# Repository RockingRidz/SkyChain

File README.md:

# SkyChain

## Current project files

- [KiCad project](pcb/SkyChain.kicad_pro), [schematic](pcb/SkyChain.kicad_sch), and [PCB](pcb/SkyChain.kicad_pcb)
- [Current Gerbers and drill files](production/gerbers.zip) — the single fabrication ZIP
- [Firmware](firmware/firmware.ino) — buttons on GPIO10 and GPIO3
- [Editable enclosure sources and STL files](cad/)
- [Revision details and validation limits](REVISION_NOTES.md)

**Enclosure fit remains unverified:** the existing case needs USB-opening clearance review before printing. CAD files have been preserved, not certified for the revised connector position. Older images below show the previous revision.

SkyChain is a compact, wearable smart keychain designed to clip onto your belt, fit in your pocket, or go anywhere with you. Whenever you spot a plane flying overhead or want to check real-time flight telemetry, SkyChain delivers live aircraft tracking data directly to your OLED screen.

## Bill of Materials (BOM)

| Part | Description | Qty | Price |
| :--- | :--- | :---: | :--- |
| ESP32-C3-DevKitM-1 | Microcontroller (U3) | 1 | \$10.00 |
| TP4056-42-ESOP8 | Battery Charger IC (U1) | 1 | \$2.00 |
| AMS1117-3.3 | LDO Voltage Regulator (U2) | 1 | \$1.50 |
| USB_C_Receptacle_USB2.0_16P | USB Interface (J1) | 1 | \$2.00 |
| Conn_01x04_Socket | Display Connector (J3) | 1 | \$1.00 |
| Conn_01x02_Socket | Battery Connector (J2) | 1 | \$1.00 |
| SW_Push | Buttons (SW1-SW3) | 3 | \$0.50 |
| Piezo Buzzer | Audio Buzzer (BZ1) | 1 | \$1.50 |
| NPN Transistor | S8050 Transistor (Q1) | 1 | \$1.00 |
| SMD Resistors | Resistors (R1-R7) | 1 | \$4.00 |
| SMD Capacitors | Capacitors (C1-C4) | 1 | \$3.00 |
| 3D Printed / Acrylic | Enclosure & Window | 1 | \$1.50 |
| **Total** | | | **\$30.00** |

---

## Overview & How It Works

SkyChain fetches live overhead tracking data via the **OpenSky Network API** to give you real-time details about aircraft above you:

- **Flight Callsign & Identification**
- **Country of Origin**
- **Altitude & Flight Height**

Every time SkyChain queries the OpenSky API or receives updated telemetry, it updates its onboard display to show current flight tracking data.

---

## Core Features

- **Real-Time Flight Tracking**: Connects via Wi-Fi to the OpenSky REST API for live aircraft callsigns, countries, and altitude metrics.
- **Interactive Multi-Function UI**: Controlled via a 2-button tactile layout supporting single clicks, double-clicks, and long-presses to navigate menus.
- **Visual Display**: Integrated high-contrast 128x64 SSD1306 OLED screen for displaying clear flight stats and system menus.
- **Autonomous Battery Management**: Onboard USB-C charging and LiPo battery regulation for untethered daily wear.
- **Compact Keychain Form Factor**: Portable, lightweight hardware layout designed for everyday carry with an integrated spline window and acrylic viewing pane.

---

## Custom Hardware Design

Designing and routing the printed circuit board and 3D-printed enclosure has been an exciting hardware challenge:

- **Microcontroller Core**: ESP32 module managing Wi-Fi requests, display driving, and button debounce logic.
- **Power System**: Lithium battery charging paired with a low-dropout regulator and USB-C power delivery.
- **Enclosure Geometry**: Custom CAD model featuring a 2.0 mm wall enclosure, reinforced keychain mount, and a recessed internal ledge for a flush-fit acrylic window.
- **Optimized Passives**: SMD passive array for power decoupling, USB pull-downs, and robust circuit stability.
- THIS WAS MY 3RD PCB DESIGN AND PROLLY THE MOST COMPLEX IVE MADE!!
-

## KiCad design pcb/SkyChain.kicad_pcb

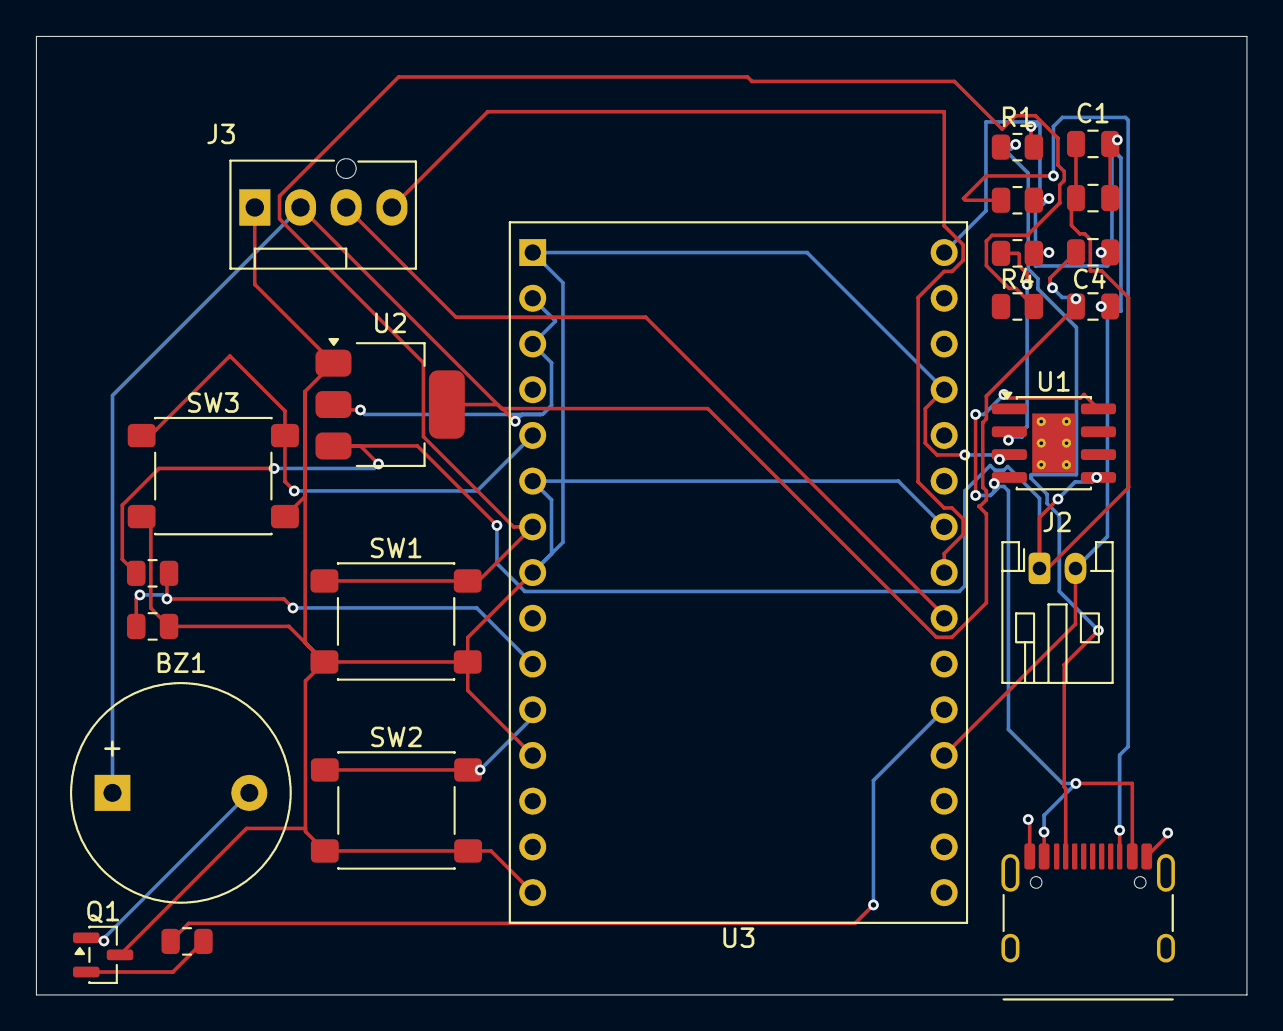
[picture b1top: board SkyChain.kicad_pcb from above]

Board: 2 copper layers, 67.2 x 53.2 mm, 22 parts (0 on the bottom side), 16 nets.

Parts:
BZ1: Buzzer; Buzzer_12x9.5RM7.6
C1, C3: 10uF; C_0805_2012Metric
C2, C4: 100nF; C_0805_2012Metric
J1: USB_C_Receptacle_USB2.0_16P; USB_C_Receptacle_HRO_TYPE-C-31-M-12
J2: Conn_01x02_Socket; JST_PH_S2B-PH-K_1x02_P2.00mm_Horizontal
J3: Conn_01x04_Socket; FanPinHeader_1x04_P2.54mm_Vertical
Q1: NPN; SOT-23
R1, R2: 5.1k; R_0805_2012Metric
R3: 1.2k; R_0805_2012Metric
R4, R5: 1k; R_0805_2012Metric
R6, R7: 100k; R_0805_2012Metric
SW1, SW2, SW3: SW_Push; SW_SPST_PTS645Sx43SMTR92
U1: TP4056-42-ESOP8; SOIC-8-1EP_3.9x4.9mm_P1.27mm_EP2.41x3.3mm_ThermalVias
U2: AMS1117-3.3; SOT-223-3_TabPin2
U3: ESP32-C3-DevKitM-1

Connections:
GND: C1.2, C2.2, C3.2, C4.2, J1.A1 (GND), J1.A12 (GND), J1.B1 (GND), J1.B12 (GND), J2.2, J3.1, Q1.3 (E), R1.2, R2.2, R3.2, R7.2, SW1.2, SW2.2, SW3.2, U1.3 (GND), U2.1 (GND), U3.1 (GND), U3.6 (GND), U3.8 (GND), U3.12 (GND), U3.15 (GND), U3.16 (GND), U3.19 (GND), U3.24 (GND), U3.27 (GND), U3.30 (GND)
unnamed: BZ1.1 (+), C3.1, C4.1, J3.2, U2.2 (VO), U3.2 (3V3), U3.3 (3V3)
unnamed: BZ1.2 (-), Q1.1 (C)
unnamed: J1.A5 (CC1), R1.1
unnamed: J1.B5 (CC2), R2.1
unnamed: C1.1, C2.1, J2.1, R6.1, U1.5 (BAT), U2.3 (VI)
unnamed: J3.3, U3.22 (IO6)
unnamed: J3.4, U3.23 (IO7)
unnamed: Q1.2 (B), R5.2
unnamed: J1.A4 (VBUS), J1.A9 (VBUS), J1.B4 (VBUS), J1.B9 (VBUS), U1.4 (V_{CC}), U1.8 (CE)
unnamed: R3.1, U1.2 (PROG)
unnamed: R6.2, R7.1, U3.10 (IO1)
unnamed: SW3.1, U3.5 (IO3)
unnamed: R5.1, U3.20 (IO4)
unnamed: SW2.1, U3.11 (IO10)
unnamed: R4.2, SW1.1, U3.7 (RST)

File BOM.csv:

Item,Qty,Supplier,Cost/item,Total Cost,link
ESP32-C3-DevKitM-1,1,Robu.in,$10.00,$10.00,https://robu.in/product/espressif-esp32-c3/
TP4056-42-ESOP8,1,Robu.in,$2.00,$2.00,https://robu.in/product/tp4056-1a-lipo-battery-charging-boar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
AMS1117-3.3,1,Robu.in,$1.50,$1.50,https://robu.in/product/ams1117-3-3-advanced-monolithic-syst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
USB_C_Receptacle_USB2.0_16P,1,Robu.in,$2.00,$2.00,https://robu.in/product/usb-3-1-type-c-female-jack-socket-co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
Conn_01x04_Socket,1,Robu.in,$1.00,$1.00,https://robu.in/product/4-pin-female-11mm-tall-stackable-hea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
Conn_01x02_Socket,1,Robu.in,$1.00,$1.00,https://robu.in/product/jst-xh-2-54mm-2-pin-female-housing-c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
SW_Push,3,Amazon.in,$0.50,$1.50,https://www.amazon.in/Tactile-Button-Momentary-Electronics-P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
Piezo Buzzer,1,Robu.in,$1.50,$1.50,https://robu.in/product/1-month-warranty-1248/
NPN Transistor,1,Robu.in,$1.00,$1.00,https://robu.in/product/s8050range160-300-jcet-25v-625mw-160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
SMD Resistors,1,Robu.in,$4.00,$4.00,https://robu.in/product/10k-ohm-1-4w-0805-surface-mount-chip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
SMD Capacitors,1,Robu.in,$3.00,$3.00,https://robu.in/product/0805b106k160nt-fh-16v-10uf-x7r%c2%b1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
3D Printed Enclosure & Acrylic,1,Robu.in,$1.50,$1.50,https://robu.in/product/3d-printing-service1/
Acrylic Sheet,1,Amazon.in,$2.00,$2.00,https://www.amazon.in/Fliptic-Acrylic-sheet-Transparent-pain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
Estimated total shipping,1,,,$1.00,
